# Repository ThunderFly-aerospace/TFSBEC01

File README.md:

# TFSBEC01 - High efficient power supply with measuring circuit for UAV

Many devices in unmanned vehicles require a quality power supply, and it is very useful to know the actual and real consumption of these components. Our TFSBEC module is designed to provide power to servos, autopilot (flight controller), and other medium-power drone accessories. In case the user needs more current or two independent sources on his drone, for example, a separate source for avionics and power-consuming elements (actuators), it is possible to chain these modules.

## Parameters

| Parameter | Value | Note |
|------|------|---------|
| Regulator technology | Switched step-down| [LMR14050](https://www.ti.com/lit/ds/symlink/lmr14050.pdf)|
| Input voltage | 6 - 40 V  | Equivalent of 2S to 9S li-pol  accumulators |
| Output voltage | 5.4 V, 5 A | based form the PX4 standard, can be adjusted |
| Regulated connector | Molex Click-n-mat 6p, JST-GH 6p | Connectors are parallel |
| In/Out connector | XT30 | max current 15 A |
| Current measurement range | 0 - 50 A | |
| Volts per Amper | 39.6 mV/A | From component datasheet |
| Current measurement Volts offset | 330 mV | From component datasheet |
| Voltage measurement range | 0 - 40 V | Depend on target ADC max input ( max. 3.95 V ) |
| Voltage measurement divider | 10.13 | From schematic |
| Size | approx. 46 x 30 mm| PCB only |
| Weight | | PCB only |
| Compatibility | Pixhawk-based drones | As a quality source, it can be operated on any drone |

## PX4 Params

These constants are nominal values taken from the datasheet:

  * A = BAT1_A_PER_V = 25.2525
  * B = BAT_V_OFFS_CURR = 0.33
  * BAT1_V_DIV = 10.13
    
QGC build-in measurement can be used to estimate parameters more precisely for the specific piece. The PX4 estimation of current is calculated from the ADC raw voltage by the following formula: 

)

For the computation of BAT_V_OFFS_CURR, multiple current measurements are usually needed, because there are significant peaks due to powering of electronics with a low current consumption.

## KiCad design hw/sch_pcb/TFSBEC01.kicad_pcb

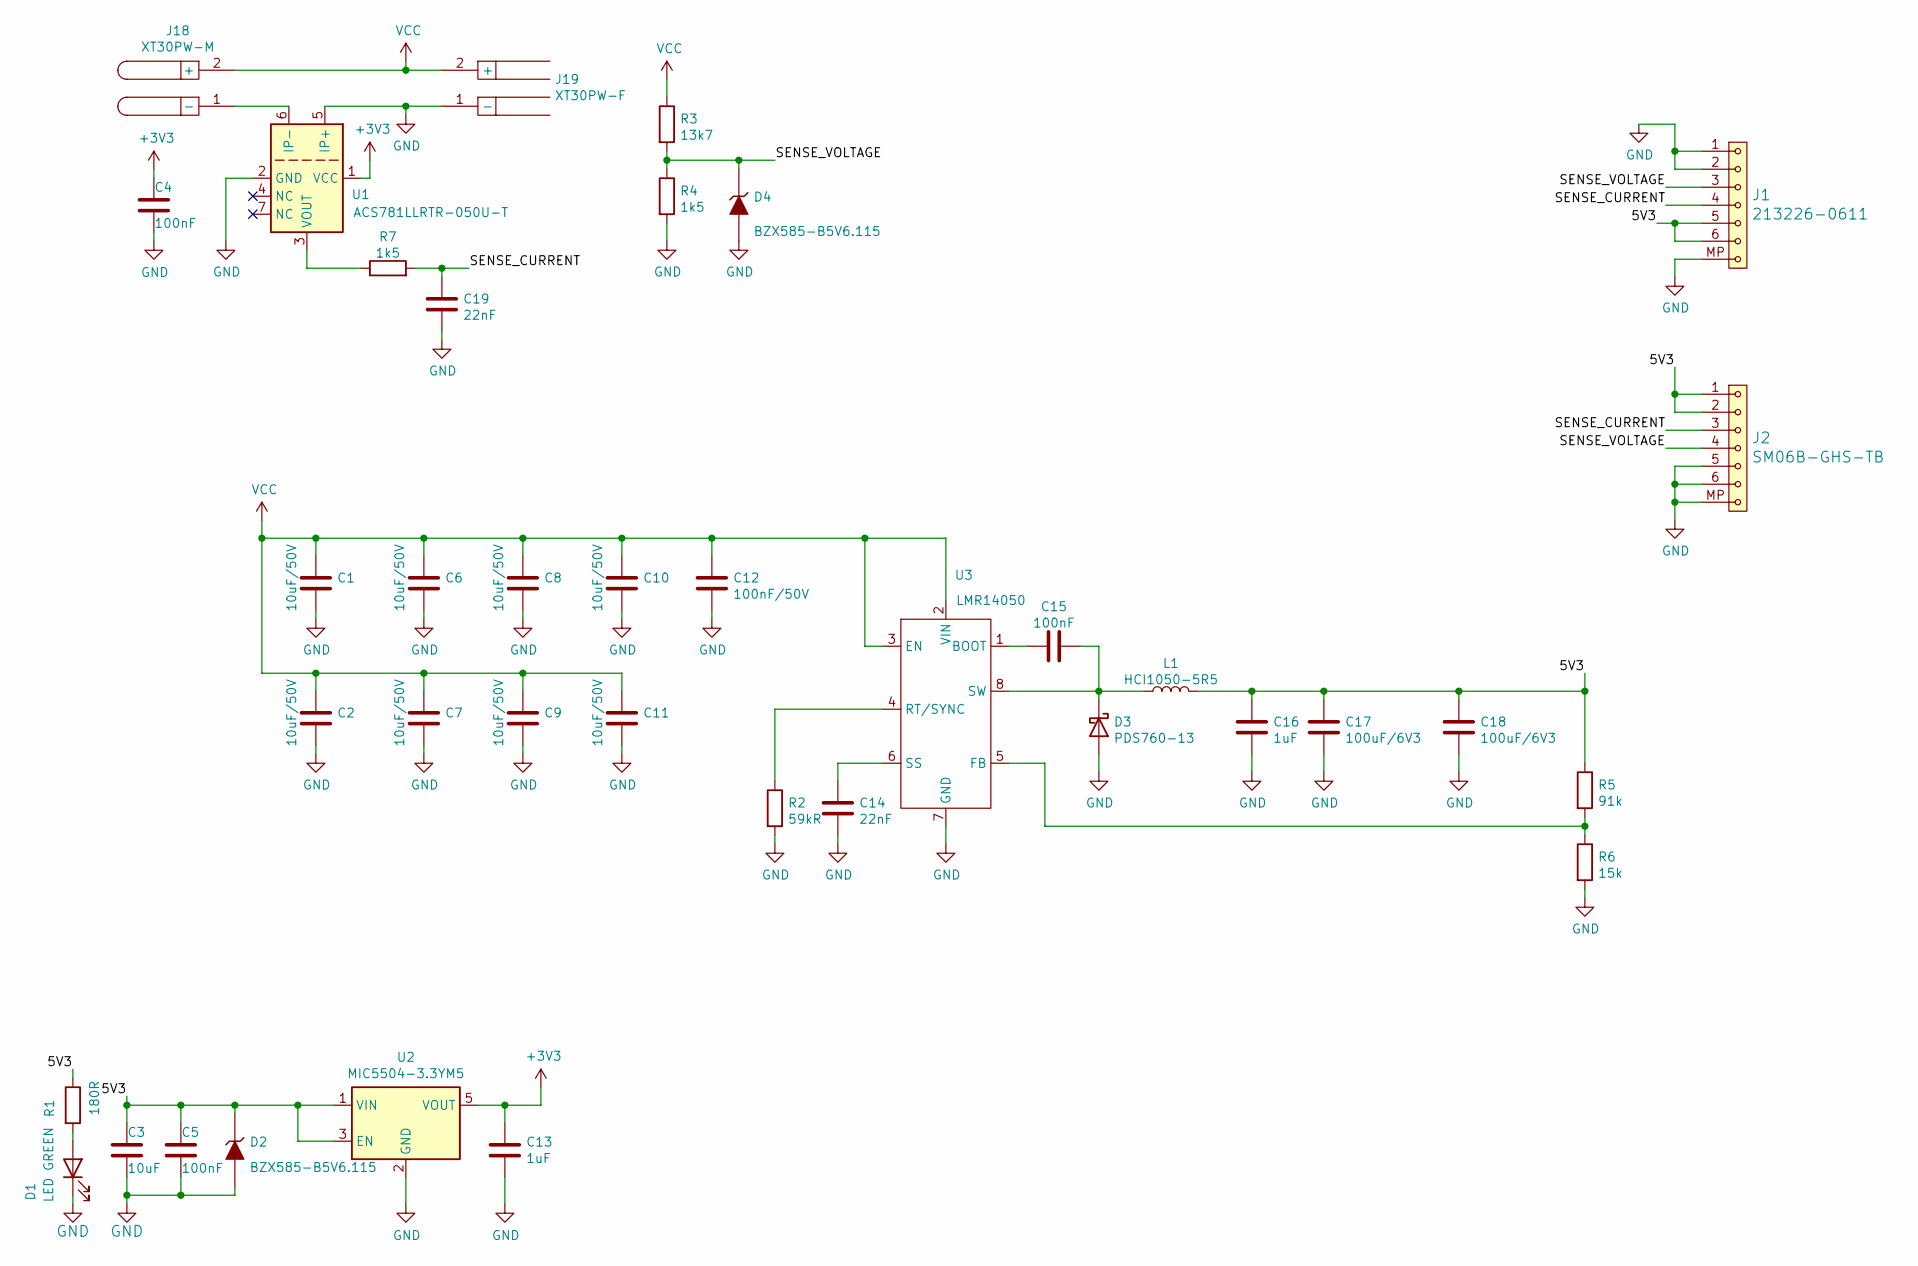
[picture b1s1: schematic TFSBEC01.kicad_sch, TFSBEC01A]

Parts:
C1, C2, C6, C7, C8, C9, C10, C11: 10uF/50V; R_1206_3216Metric
C3: 10uF; SMD-0805
C4, C5, C15: 100nF; SMD-0805
C12: 100nF/50V; SMD-0805
C13, C16: 1uF; SMD-0805
C14, C19: 22nF; SMD-0805
C17, C18: 100uF/6V3; R_1206_3216Metric
D1: LED GREEN; LED_1206
D2, D4: BZX585-B5V6.115; D_SOD-523
D3: PDS760-13; D_PowerDI-5
J1: 213226-0611; Molex_CLIK-Mate_505405-0670_1x06-1MP_P1.50mm_Vertical
J2: SM06B-GHS-TB; JST_GH_SM06B-GHS-TB_1x06-1MP_P1.25mm_Horizontal
J18: XT30PW-M; AMASS_XT30PW-M_1x02_P2.50mm_Horizontal
J19: XT30PW-F; AMASS_XT30PW-F_1x02_P2.50mm_Horizontal
L1: HCI1050-5R5; L_Wuerth_HCI-1050
R1: 180R; SMD-0805
R2: 59kR; SMD-0805
R3: 13k7; SMD-0805
R4, R7: 1k5; SMD-0805
R5: 91k; SMD-0805
R6: 15k; SMD-0805
U1: ACS781LLRTR-050U-T; Allegro_PSOF-7_4.8x6.4mm_P1.60mm
U2: MIC5504-3.3YM5; SOT-23-5
U3: LMR14050; SOIC-8-1EP_3.9x4.9mm_P1.27mm_EP2.41x3.3mm_ThermalVias

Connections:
+3V3: C4.1, C13.1, U1.1 (VCC), U2.5 (VOUT)
/5V3: C3.1, C5.1, C16.1, C17.1, C18.1, D2.1 (K), J1.5, J1.6, J2.1, J2.2, L1.2, R1.1, R5.1, U2.1 (VIN), U2.3 (EN)
/SENSE_CURRENT: C19.1, J1.4, J2.3, R7.2
/SENSE_VOLTAGE: D4.1 (K), J1.3, J2.4, R3.2, R4.1
GND: C1.2, C2.2, C3.2, C4.2, C5.2, C6.2, C7.2, C8.2, C9.2, C10.2, C11.2, C12.2, C13.2, C14.2, C16.2, C17.2, C18.2, C19.2, D1.1 (K), D2.2 (A), D3.2 (A), D4.2 (A), J1.1, J1.2, J1.MP, J2.5, J2.6, J2.MP, J19.1 (-), R2.2, R4.2, R6.2, U1.2 (GND), U1.5 (IP+), U2.2 (GND), U3.7 (GND), U3.9 (GND)
unnamed: C14.1, U3.6 (SS)
unnamed: C15.1, U3.1 (BOOT)
unnamed: C15.2, D3.1 (K), L1.1, U3.8 (SW)
unnamed: D1.2 (A), R1.2
unnamed: J18.1 (-), U1.6 (IP-)
unnamed: R2.1, U3.4 (RT/SYNC)
unnamed: R5.2, R6.1, U3.5 (FB)
unnamed: R7.1, U1.3 (VOUT)
VCC: C1.1, C2.1, C6.1, C7.1, C8.1, C9.1, C10.1, C11.1, C12.1, J18.2 (+), J19.2 (+), R3.1, U3.2 (VIN), U3.3 (EN)

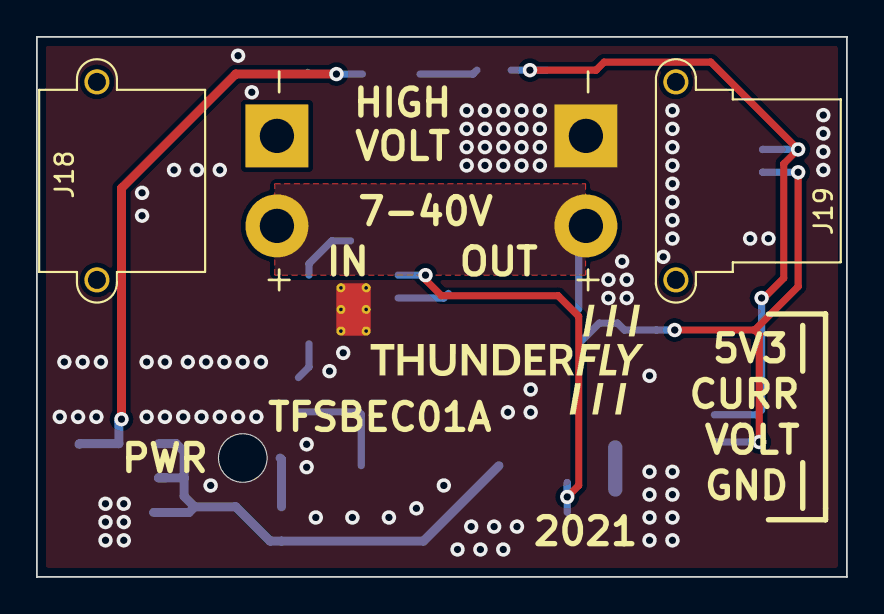
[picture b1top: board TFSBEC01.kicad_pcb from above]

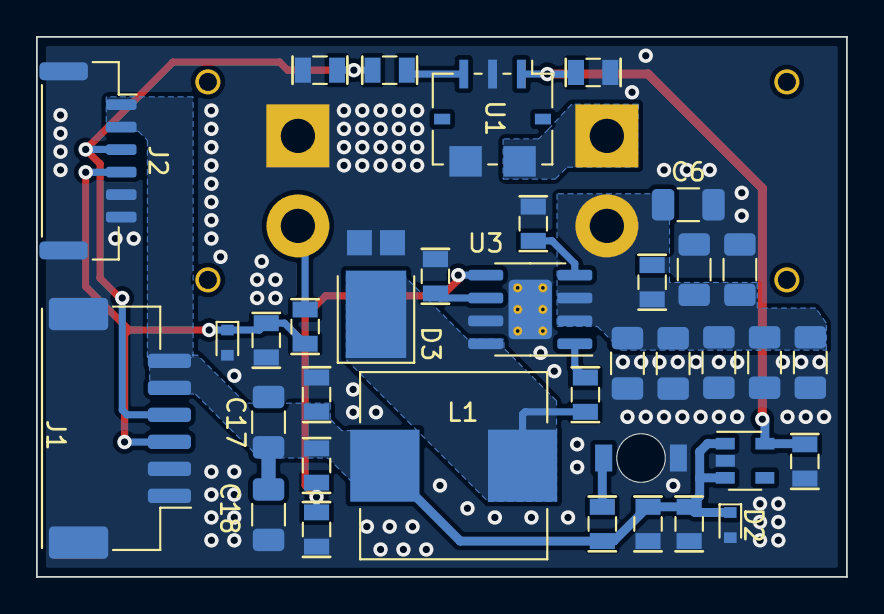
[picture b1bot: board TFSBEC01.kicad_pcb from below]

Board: 2 copper layers, 45.0 x 30.0 mm, 38 parts (36 on the bottom side), 14 nets.

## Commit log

2021-01-04 Tvorba schéma
2021-03-09 Edit
2021-04-05 Title block update.
2021-04-18 Edit shema
2021-04-25 Edit PCB
2021-04-26 Add PCB dimensions.
2022-03-15 Update project to KiCAD 6.0. Update title block.
2022-03-30 update gitignore, gitmodules, assets
2022-03-30 actions
2022-03-30 Update actions products
2023-10-07 Convert to KiCAD7 Improve schematics layout Add link to datasheet.
2023-10-07 Enable automatic action update.
2023-10-07 Update workflow.
2023-10-07 Update README.md
    Add link to images.
2023-10-07 Remove revision from project files name.
2023-10-07 switched dimensions to comments layer.
2024-03-05 Crop black border from image.
2024-07-21 Update to KiCADv8. Improve documentation.
2024-09-16 Update README.md
    Improve readibility.
2024-09-16 Update README.md
    cleanup formula.
2024-09-16 Update README.md
    Fix equation rendering to avoid \text{} syntax, which seems to break the GitHub URL caching engine.
2024-09-16 Commit datasheets of key components.
